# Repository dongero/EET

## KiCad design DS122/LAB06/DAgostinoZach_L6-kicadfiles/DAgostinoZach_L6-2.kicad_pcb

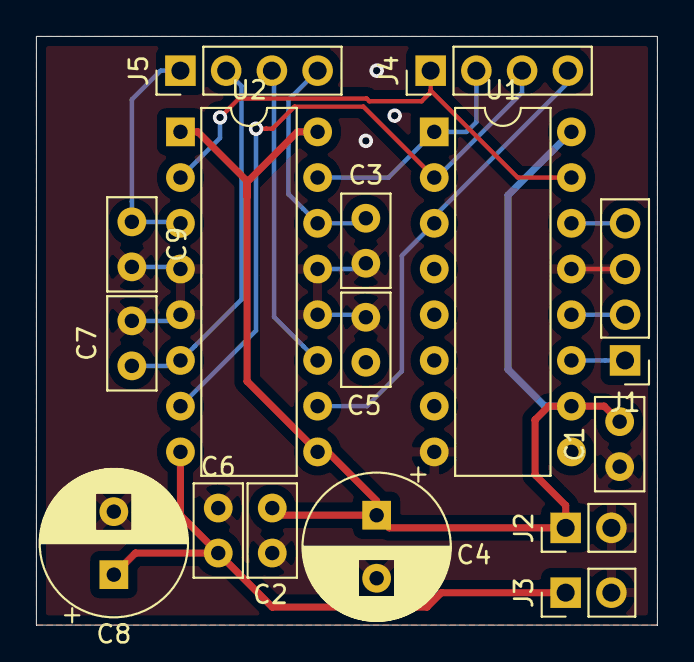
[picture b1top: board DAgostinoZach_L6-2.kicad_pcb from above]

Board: 2 copper layers, 34.5 x 32.7 mm, 16 parts (0 on the bottom side), 14 nets.

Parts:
C1, C2, C3, C5, C6, C7, C9: 0.1uF; C_Disc_D5.0mm_W2.5mm_P2.50mm
C4, C8: 100uF; CP_Radial_D8.0mm_P3.50mm
J1: Data; PinHeader_1x04_P2.54mm_Vertical
J2: +5V IN; PinHeader_1x02_P2.54mm_Vertical
J3: +V Motor; PinHeader_1x02_P2.54mm_Vertical
J4: Dbug; PinHeader_1x04_P2.54mm_Vertical
J5: Out; PinHeader_1x04_P2.54mm_Vertical
U1: 74LS595; DIP-16_W7.62mm
U2: L293; DIP-16_W7.62mm

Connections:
+5V: C1.2, C2.1, C4.1, J2.1, U1.10, U1.16, U2.1, U2.9, U2.16
/QA: J4.1, U1.15, U2.2
/QB: J4.2, U1.1, U2.15
/QC: J4.3, U1.2, U2.7
/QD: J4.4, U1.3, U2.10
/RCLK: J1.2, U1.12
/SER: J1.4, U1.14
/SRCLK: J1.1, U1.11
/X1-1: C7.1, J5.2, U2.6
/X1-2: C9.1, J5.1, U2.3
/X1-3: C3.1, J5.4, U2.14
/X1-4: C5.1, J5.3, U2.11
GND: C1.1, C2.2, C3.2, C4.2, C5.2, C6.2, C7.2, C8.2, C9.2, J1.3, J2.2, J3.2, U1.8, U1.13, U2.4, U2.5, U2.12, U2.13
Vdrive: C6.1, C8.1, J3.1, U2.8

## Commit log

2020-05-22 added files
2020-07-13 updating files
